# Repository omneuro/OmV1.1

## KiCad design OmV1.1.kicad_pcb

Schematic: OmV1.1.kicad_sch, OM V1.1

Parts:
C1: 2u2; C_01005_0402Metric; Manufacturer Part # GRM155R61C225KE44D
C2, C5, C6, C8, C10, C15, C25: 2u2; C_0402_1005Metric
C3, C4, C7, C11, C13: 10u; C_0603_1608Metric
C9: 0u01; C_0402_1005Metric
C12: 0u1; C_01005_0402Metric
C14, C17: 2.2nf; C_0402_1005Metric
C16, C18, C19, C20, C21, C22: 100nf; C_0402_1005Metric
C23, C24: 27pf; C_0402_1005Metric
C26: 100u; C_0402_1005Metric
C27, C29, C30, C36, C38, C40, C42: 1u; C_0402_1005Metric
C28, C32, C35, C37, C39, C41: 0u1; C_0402_1005Metric
C31, C50, C55, C58: 10nf; C_0402_1005Metric
C33: 10u; C_0402_1005Metric
C34: 1n; C_0402_1005Metric
C43, C44, C45, C46, C47: CA0508KRX7R7BB103; CA0508K4X7R7BB103
C48, C51, C56, C59: 0.1uf; C_0402_1005Metric
C49, C52, C57, C60: 2uf; C_0402_1005Metric
C53, C54: 5uf; C_0402_1005Metric
D1: CDBU0130L
D2: LED; LED_0201_0603Metric_Pad0.64x0.40mm_HandSolder
D3: SMBJ5.0A; DIOM4336X265N; PARTREV F2102
FB1: BLM15AG221SN1D; R_0402_1005Metric
H1, H2, H3: MountingHole; MountingHole_2.2mm_M2
J1: Conn_01x02_Socket; PinHeader_1x02_P2.54mm_Vertical
J2: GSB1C41110SSHR; AMPHENOL_GSB1C41110SSHR; PARTREV AX1
J3: 5788800-2; CONN_5788800-2_TEC
J4: TC2030; Tag-Connect_TC2030-IDC-NL_2x03_P1.27mm_Vertical
J5, J6, J7, J8, J9, J10, J11, J12: Conn_01x01_Pin; PinHeader_1x01_P2.54mm_Vertical
R1, R3: 5.1k; R_0402_1005Metric
R2: 1M; R_0402_1005Metric
R6: 10k; R_0402_1005Metric
R7: 220; R_0402_1005Metric
R8: 10M; R_0402_1005Metric
R9, R10, R11, R12, R13: CAY16-2201F4LF; RESCAF80P320X160X60-8N
U1: MCP1754T-3302E/OT; SOT-23-5_MC_MCH
U2: LM2664M6; SOT-23-6
U3: TPS72325DBV; SOT-23-5
U4: TLV70025_SOT23-5; SOT-23-5
U5: LIS3DH; LGA-16_3x3mm_P0.5mm_LayoutBorder3x5y
U6: SN74LVC1G32DCKR; DCK5
U7: USBLC6-2SC6; SOT-23-6
U8: STM32F446RETx; LQFP-64_10x10mm_P0.5mm
U9: ADS1298xPAG; TQFP-64_10x10mm_P0.5mm
U10, U11, U12, U13, U14, U15: TPD4E1B06DCKR; DCK6_TEX
U16: ISOUSB211DPR; DP0028A-IPC_C
XTAL1: ABM3-8.000MHZ-D2Y-T; XTAL_ABM3-8.000MHZ-D2Y-T_ABR

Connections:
+3.3V: C2.1, C5.1, C12.2, C13.2, C15.1, C16.1, C17.1, C18.1, C19.1, C20.1, C21.1, C22.1, C39.1, C40.1, J4.1, J5.1, U1.5 (VOUT), U2.4 (SD), U2.5 (V+), U4.1 (IN), U4.3 (EN), U5.1 (VDD_IO), U5.14 (VDD), U6.5 (VCC), U7.5 (VBUS), U8.1 (VBAT), U8.13 (VDDA), U8.19 (VDD), U8.32 (VDD), U8.48 (VDD), U8.64 (VDD), U9.35 (~PWDN), U9.48 (DVDD), U9.50 (DVDD), U9.52 (CLKSEL), U16.16 (CDPEN2_N), U16.24 (VCC2), U16.27 (V3P3V2), U16.28 (VBUS2)
/1N: J3.15, R12.4, U14.2 (IO2)
/1P: J3.2, R13.1, U15.5 (IO4)
/2N: J3.16, R12.2, U14.5 (IO4)
/2P: J3.3, R12.3, U14.1 (IO1)
/3N: J3.17, R11.4, U13.1 (IO1)
/3P: J3.4, R12.1, U13.2 (IO2)
/4N: J3.18, R11.2, U13.5 (IO4)
/4P: J3.5, R11.3, U13.4 (IO3)
/5N: J3.19, R10.4, U12.1 (IO1)
/5P: J3.6, R11.1, U12.2 (IO2)
/6N: J3.20, R10.2, U12.5 (IO4)
/6P: J3.7, R10.3, U12.4 (IO3)
/7N: J3.21, R9.4, U11.1 (IO1)
/7P: J3.8, R10.1, U11.2 (IO2)
/8N: J3.22, R9.2, U11.5 (IO4)
/8P: J3.9, R9.3, U11.4 (IO3)
/+2.5V: C6.1, C7.1, C35.1, C36.1, C37.1, C38.1, C41.1, C42.1, J3.11, J3.24, J7.1, U4.5 (OUT), U9.19 (AVDD), U9.21 (AVDD), U9.22 (AVDD), U9.54 (AVDD1), U9.56 (AVDD), U9.59 (AVDD), U10.4 (IO3)
/+3.3V_ISO: C54.1, U16.2 (V3P3V1), U16.13 (CDPEN1_N)
/-2.5V: C10.1, C11.1, C26.2, C27.2, C28.2, C29.2, C30.2, C32.2, C33.2, J3.12, J3.25, J8.1, U3.5 (OUT), U9.20 (AVSS), U9.23 (AVSS), U9.25 (VREFN), U9.32 (AVSS), U9.53 (AVSS1), U9.57 (AVSS), U9.58 (AVSS), U10.2 (IO2)
/-3.3V: C4.1, C8.1, J6.1, U2.2 (OUT), U3.2 (IN), U3.3 (EN)
/BIAS: J3.10, J3.23, R9.1, U10.5 (IO4)
/BIAS_DRV: C34.2, C43.5, R8.2, R9.8
/BIAS_IN: C34.1, R8.1, U9.62 (RLDIN), U9.63 (RLDOUT)
/CC1_R: J2.A5 (CC1), R1.2
/CC2_R: J2.B5 (CC2), R3.1
/CS1: U8.25 (PC5), U9.39 (~CS)
/CS2: U5.8 (CS), U6.2 (B), U8.34 (PB13)
/DRDY: U8.16 (PA2), U9.47 (~DRDY)
/IN1N: C46.8, R12.5, U9.15 (IN1N)
/IN1P: C47.5, R13.8, U9.16 (IN1P)
/IN2N: C46.6, R12.7, U9.13 (IN2N)
/IN2P: C46.7, R12.6, U9.14 (IN2P)
/IN3N: C45.8, R11.5, U9.11 (IN3N)
/IN3P: C46.5, R12.8, U9.12 (IN3P)
/IN4N: C45.6, R11.7, U9.9 (IN4N)
/IN4P: C45.7, R11.6, U9.10 (IN4P)
/IN5N: C44.8, R10.5, U9.7 (IN5N)
/IN5P: C45.5, R11.8, U9.8 (IN5P)
/IN6N: C44.6, R10.7, U9.5 (IN6N)
/IN6P: C44.7, R10.6, U9.6 (IN6P)
/IN7N: C43.8, R9.5, U9.3 (IN7N)
/IN7P: C44.5, R10.8, U9.4 (IN7P)
/IN8N: C43.6, R9.7, U9.1 (IN8N)
/IN8P: C43.7, R9.6, U9.2 (IN8P)
/INT1: U5.11 (INT1), U8.33 (PB12)
/IN_SRB1: C47.6, R13.7, U9.17 (TESTP_PACE_OUT1)
/IN_SRB2: C47.7, R13.6, U9.18 (TESTP_PACE_OUT2)
/MISO: J10.1, U5.7 (SDO), U8.22 (PA6), U9.43 (DOUT)
/MOSI: J11.1, U6.1 (A), U8.23 (PA7), U9.34 (DIN)
/OR_OUT: U5.6 (SDI), U6.4 (Y)
/RAW: D1.2 (A), J1.1
/RESET: U8.28 (PB2), U9.36 (~RESET)
/SCLK: J9.1, U5.4 (SPC), U8.21 (PA5), U9.40 (SCLK)
/SRB1: J3.1, R13.2, U15.4 (IO3)
/SRB2: J3.14, R13.3, U15.2 (IO2)
/START: U8.26 (PB0), U9.38 (START)
/SWD_CLK: J4.6, U8.49 (PA14)
/SWD_DIO: J4.2, U8.46 (PA13)
/SWD_NRST: J4.4, U8.7 (NRST)
/SWD_TRC: J4.3, U8.55 (PB3)
/USB+: U8.44 (PA11), U16.21 (DD+)
/USB-: U8.45 (PA12), U16.22 (DD-)
/USBLC_+: J2.A6 (DP1), J2.B6 (DP2), U7.3 (I/O2)
/USBLC_-: J2.A7 (DN1), J2.B7 (DN2), U7.1 (I/O1)
/USB_ISO+: U7.6 (I/O1), U16.8 (UD+)
/USB_ISO-: U7.4 (I/O2), U16.7 (UD-)
/VBUS: C53.2, FB1.2, U16.1 (VBUS1), U16.5 (VCC1)
/VCAP1: C26.1, U9.28 (VCAP1)
/VCAP2: C27.1, U9.30 (VCAP2)
/VCAP3: C28.1, C29.1, U9.55 (VCAP3)
/VCAP4: C30.1, U9.26 (VCAP4)
/VDD_OK: U8.43 (PA10), U16.23 (V1OK)
/VIN: C1.1, D1.1 (K), U1.1 (VIN), U1.3 (*SHDN)
/XTAL_IN: C23.1, U8.5 (PH0), XTAL1.1
/XTAL_OUT: C24.1, U8.6 (PH1), XTAL1.2
GND: C1.2, C2.2, C4.2, C5.2, C6.2, C7.2, C8.2, C9.2, C10.2, C11.2, C12.1, C13.1, C15.2, C16.2, C17.2, C18.2, C19.2, C20.2, C21.2, C22.2, C23.2, C24.2, C25.2, C31.2, C35.2, C36.2, C37.2, C38.2, C39.2, C40.2, C41.2, C42.2, C43.1, C43.2, C43.3, C43.4, C44.1, C44.2, C44.3, C44.4, C45.1, C45.2, C45.3, C45.4, C46.1, C46.2, C46.3, C46.4, C47.1, C47.2, C47.3, C47.4, C47.8, C48.2, C49.2, C50.2, C51.2, C52.2, J1.2, J3.13, J4.5, J12.1, R6.1, R7.1, R13.4, R13.5, U1.2 (GND), U2.1 (GND), U3.1 (GND), U4.2 (GND), U5.5 (GND), U5.10 (GND), U5.12 (GND), U6.3 (GND), U8.12 (VSSA), U8.18 (VSS), U8.31 (VSS), U8.47 (VSS), U8.63 (VSS), U9.31 (RESV1), U9.33 (DGND), U9.41 (DAISY_IN), U9.49 (DGND), U9.51 (DGND), U9.60 (RLDREF), U10.3 (GND), U11.3 (GND), U12.3 (GND), U13.3 (GND), U14.3 (GND), U15.3 (GND), U16.17 (GND2), U16.19 (EQ21), U16.20 (EQ20), U16.26 (GND2)
GND_USB: C14.2, C53.1, C54.2, C55.2, C56.2, C57.2, C58.2, C59.2, C60.2, D3.A, J2.A1_B12 (GND_A), J2.B1_A12 (GND_B), R1.1, R2.1, R3.2, U7.2 (GND), U16.3 (GND1), U16.9 (EQ10), U16.10 (EQ11), U16.12 (GND1)
unnamed: C14.1, J2.SH1 (SHIELD), J2.SH2 (SHIELD), J2.SH3 (SHIELD), J2.SH4 (SHIELD), R2.2
unnamed: C31.1, C48.1, C49.1, C50.1, C51.1, C52.1, U16.18 (V1P8V2), U16.25 (V1P8V2)
unnamed: C55.1, C56.1, C57.1, C58.1, C59.1, C60.1, U16.4 (V1P8V1), U16.11 (V1P8V1)
unnamed: D2.2 (A), U8.38 (PC7)
unnamed: D2.1 (K), R7.2
unnamed: D3.C, FB1.1, J2.A4_B9 (VBUS_A), J2.B4_A9 (VBUS_B)
unnamed: C3.1, U2.6 (CAP+)
unnamed: C3.2, U2.3 (CAP-)
unnamed: C9.1, U3.4 (NR)
unnamed: R6.2, U8.60 (BOOT0)
unnamed: C25.1, U8.30 (VCAP_1)
unnamed: C32.1, C33.1, U9.24 (VREFP)

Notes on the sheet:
USB Isolator
ADC
USB C (Data Output)
POWER STAGE
TVS CIRCUITRY
MCU
CONNECTORS & POWER DECOUPLING
ACC & GYRO

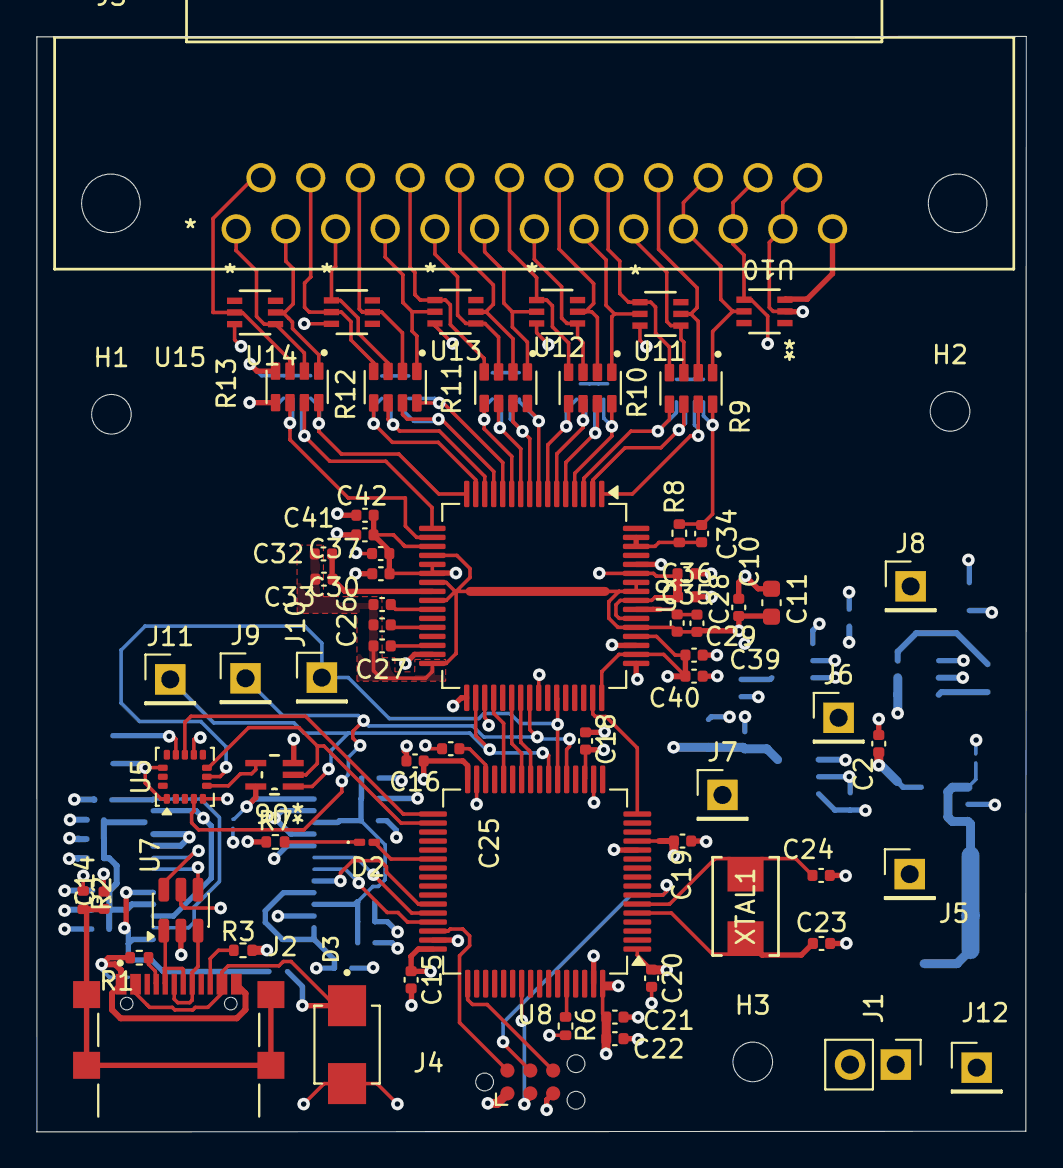
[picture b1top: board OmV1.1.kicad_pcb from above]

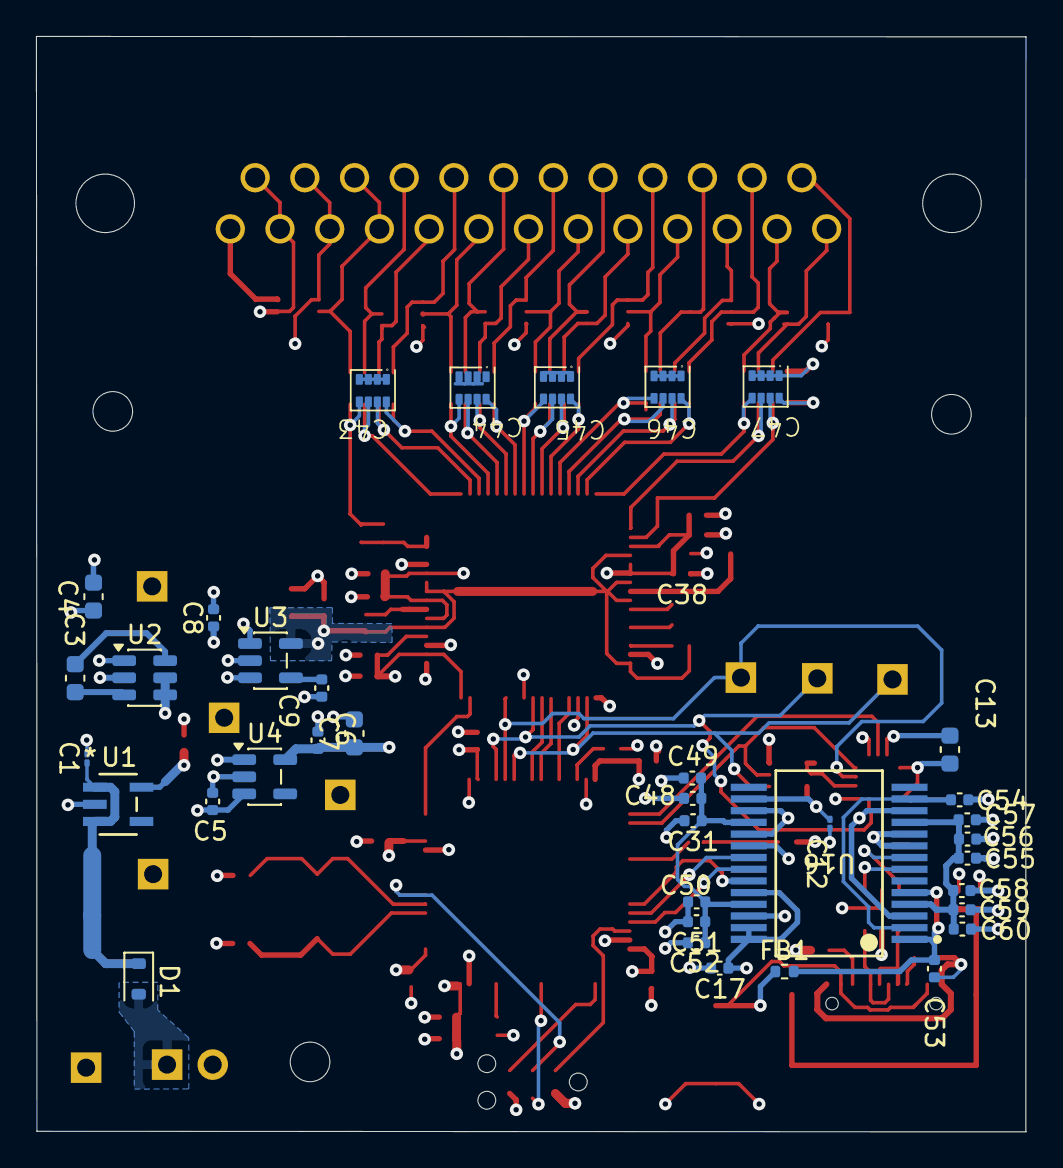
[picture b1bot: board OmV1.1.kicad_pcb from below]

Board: 4 copper layers, 55.0 x 60.9 mm, 107 parts (37 on the bottom side), 90 nets.

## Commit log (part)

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2025-11-23 file update
